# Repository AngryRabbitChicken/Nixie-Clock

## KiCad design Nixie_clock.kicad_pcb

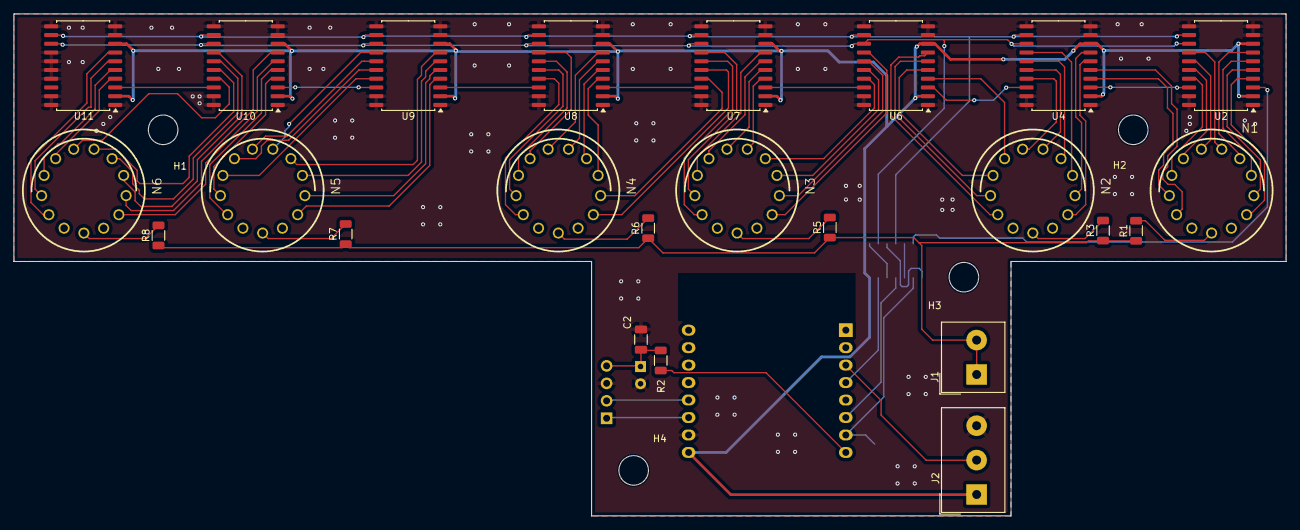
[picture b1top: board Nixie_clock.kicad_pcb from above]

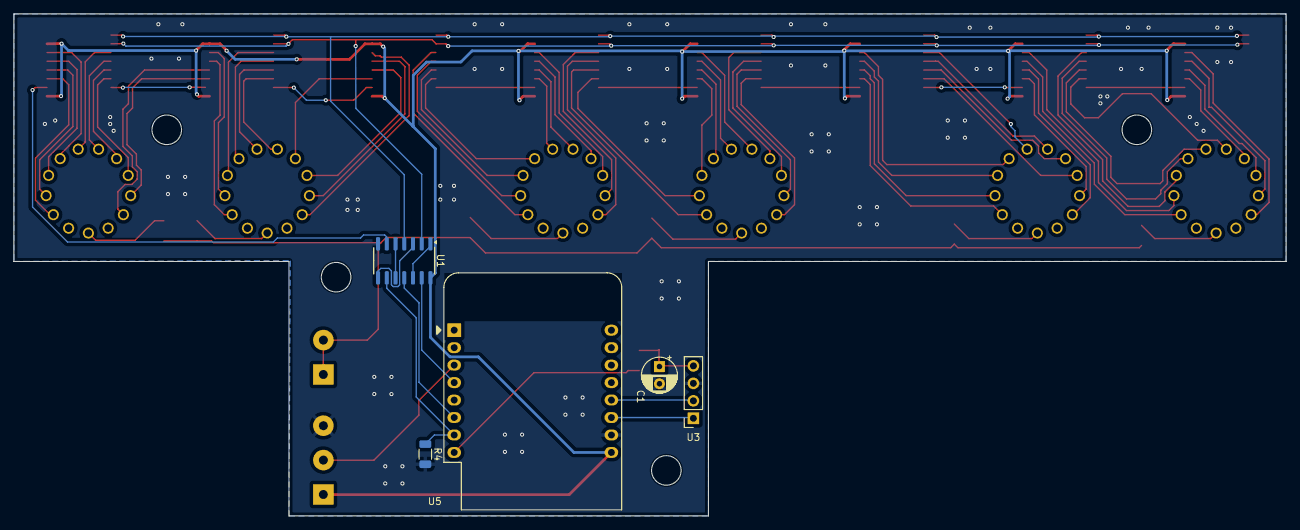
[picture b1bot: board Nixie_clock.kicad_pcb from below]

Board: 2 copper layers, 185.0 x 73.0 mm, 33 parts (5 on the bottom side), 90 nets.

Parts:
C1: 10µ; CP_Radial_D5.0mm_P2.50mm
C2: 1µ; C_1206_3216Metric
H1, H2, H3, H4: MountingHole; MountingHole_4.3mm_M4
J1: Screw_Terminal_01x02; Altech_AK100_1x02_P5.00mm
J2: Screw_Terminal_01x03; Altech_AK100_1x03_P5.00mm
N1, N2, N3, N4, N5, N6: IN-14; nixies-us-IN-14_1.1mm_holes
R1, R3, R5, R6, R7, R8: 21.5k; R_1206_3216Metric
R2: 100; R_1206_3216Metric
R4: 10k; R_1206_3216Metric
U1: 74HCT04; SO-14_3.9x8.65mm_P1.27mm
U2, U4, U6, U7, U8, U9, U10, U11: TPIC6B595; SOIC-20W_7.5x12.8mm_P1.27mm
U3: Pollin_DCF1; PinSocket_1x04_P2.54mm_Vertical
U5: WeMos_D1_mini; WEMOS_D1_mini_light

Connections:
167V: J1.1, J1.2, R1.1, R3.1, R5.1, R6.1, R7.1, R8.1
+3.3V: R2.1, U5.8 (3V3)
+5V: J2.1, U1.14 (VCC), U2.2 (VCC), U2.8 (~SRCLR), U4.2 (VCC), U4.8 (~SRCLR), U5.9 (5V), U6.2 (VCC), U6.8 (~SRCLR), U7.2 (VCC), U7.8 (~SRCLR), U8.2 (VCC), U8.8 (~SRCLR), U9.2 (VCC), U9.8 (~SRCLR), U10.2 (VCC), U10.8 (~SRCLR), U11.2 (VCC), U11.8 (~SRCLR)
/N1-A: N1.A, R1.2
/N2-A: N2.A, R3.2
/N3-A: N3.A, R5.2
/N4-A: N4.A, R6.2
/N5-A: N5.A, R7.2
/N6-A: N6.A, R8.2
/U2-D0: N1.1, U2.4 (DRAIN0)
/U2-D1: N1.2, U2.5 (DRAIN1)
/U2-D2: N1.3, U2.6 (DRAIN2)
/U2-D3: N1.4, U2.7 (DRAIN3)
/U2-D4: N1.5, U2.14 (DRAIN4)
/U2-D5: N1.6, U2.15 (DRAIN5)
/U2-D6: N1.7, U2.16 (DRAIN6)
/U2-D7: N1.8, U2.17 (DRAIN7)
/U4-D0: N1.9, U4.4 (DRAIN0)
/U4-D1: N1.0, U4.5 (DRAIN1)
/U4-D2: N2.1, U4.6 (DRAIN2)
/U4-D3: N2.2, U4.7 (DRAIN3)
/U4-D4: N2.3, U4.14 (DRAIN4)
/U4-D5: N2.4, U4.15 (DRAIN5)
/U4-D6: N2.5, U4.16 (DRAIN6)
/U4-D7: N2.6, U4.17 (DRAIN7)
/U6-D0: N2.7, U6.4 (DRAIN0)
/U6-D1: N2.8, U6.5 (DRAIN1)
/U6-D2: N2.9, U6.6 (DRAIN2)
/U6-D3: N2.0, U6.7 (DRAIN3)
/U6-D4: N3.1, U6.14 (DRAIN4)
/U6-D5: N3.2, U6.15 (DRAIN5)
/U6-D6: N3.3, U6.16 (DRAIN6)
/U6-D7: N3.4, U6.17 (DRAIN7)
/U7-D0: N3.5, U7.4 (DRAIN0)
/U7-D1: N3.6, U7.5 (DRAIN1)
/U7-D2: N3.7, U7.6 (DRAIN2)
/U7-D3: N3.8, U7.7 (DRAIN3)
/U7-D4: N3.9, U7.14 (DRAIN4)
/U7-D5: N3.0, U7.15 (DRAIN5)
/U7-D6: N4.1, U7.16 (DRAIN6)
/U7-D7: N4.2, U7.17 (DRAIN7)
/U8-D0: N4.3, U8.4 (DRAIN0)
/U8-D1: N4.4, U8.5 (DRAIN1)
/U8-D2: N4.5, U8.6 (DRAIN2)
/U8-D3: N4.6, U8.7 (DRAIN3)
/U8-D4: N4.7, U8.14 (DRAIN4)
/U8-D5: N4.8, U8.15 (DRAIN5)
/U8-D6: N4.9, U8.16 (DRAIN6)
/U8-D7: N4.0, U8.17 (DRAIN7)
/U9-D0: N5.1, U9.4 (DRAIN0)
/U9-D1: N5.2, U9.5 (DRAIN1)
/U9-D2: N5.3, U9.6 (DRAIN2)
/U9-D3: N5.4, U9.7 (DRAIN3)
/U9-D4: N5.5, U9.14 (DRAIN4)
/U9-D5: N5.6, U9.15 (DRAIN5)
/U9-D6: N5.7, U9.16 (DRAIN6)
/U9-D7: N5.8, U9.17 (DRAIN7)
/U10-D0: N5.9, U10.4 (DRAIN0)
/U10-D1: N5.0, U10.5 (DRAIN1)
/U10-D2: N6.1, U10.6 (DRAIN2)
/U10-D3: N6.2, U10.7 (DRAIN3)
/U10-D4: N6.3, U10.14 (DRAIN4)
/U10-D5: N6.4, U10.15 (DRAIN5)
/U10-D6: N6.5, U10.16 (DRAIN6)
/U10-D7: N6.6, U10.17 (DRAIN7)
/U11-D0: N6.7, U11.4 (DRAIN0)
/U11-D1: N6.8, U11.5 (DRAIN1)
/U11-D2: N6.9, U11.6 (DRAIN2)
/U11-D3: N6.0, U11.7 (DRAIN3)
GND: C1.2, C2.2, J2.3, R4.2, U1.7 (GND), U2.1 (PGND), U2.9 (~G), U2.10 (PGND), U2.11 (PGND), U2.19 (LGND), U2.20 (PGND), U3.3 (GND), U4.1 (PGND), U4.9 (~G), U4.10 (PGND), U4.11 (PGND), U4.19 (LGND), U4.20 (PGND), U5.10 (GND), U6.1 (PGND), U6.9 (~G), U6.10 (PGND), U6.11 (PGND), U6.19 (LGND), U6.20 (PGND), U7.1 (PGND), U7.9 (~G), U7.10 (PGND), U7.11 (PGND), U7.19 (LGND), U7.20 (PGND), U8.1 (PGND), U8.9 (~G), U8.10 (PGND), U8.11 (PGND), U8.19 (LGND), U8.20 (PGND), U9.1 (PGND), U9.9 (~G), U9.10 (PGND), U9.11 (PGND), U9.19 (LGND), U9.20 (PGND), U10.1 (PGND), U10.9 (~G), U10.10 (PGND), U10.11 (PGND), U10.19 (LGND), U10.20 (PGND), U11.1 (PGND), U11.9 (~G), U11.10 (PGND), U11.11 (PGND), U11.14 (DRAIN4), U11.15 (DRAIN5), U11.16 (DRAIN6), U11.17 (DRAIN7), U11.19 (LGND), U11.20 (PGND)
HV_ENABLE: J2.2, U5.3 (D0)
unnamed: U1.1, U1.12
unnamed: U1.3, U1.8
unnamed: U1.5, U1.10
unnamed: U1.6, U2.3 (SER_IN)
unnamed: U2.18 (SER_OUT), U4.3 (SER_IN)
unnamed: U3.1 (PON), U5.11 (D4)
unnamed: U3.2 (TCO), U5.12 (D3)
unnamed: C1.1, C2.1, R2.2, U3.4 (VCC)
unnamed: U4.18 (SER_OUT), U6.3 (SER_IN)
unnamed: R4.1, U1.9, U5.7 (CS/D8)
unnamed: U1.11, U5.6 (MOSI/D7)
unnamed: U1.13, U5.4 (SCK/D5)
unnamed: U6.18 (SER_OUT), U7.3 (SER_IN)
unnamed: U7.18 (SER_OUT), U8.3 (SER_IN)
unnamed: U8.18 (SER_OUT), U9.3 (SER_IN)
unnamed: U1.4, U2.12 (RCLK), U4.12 (RCLK), U6.12 (RCLK), U7.12 (RCLK), U8.12 (RCLK), U9.12 (RCLK), U10.12 (RCLK), U11.12 (RCLK)
unnamed: U9.18 (SER_OUT), U10.3 (SER_IN)
unnamed: U10.18 (SER_OUT), U11.3 (SER_IN)
unnamed: U1.2, U2.13 (SRCK), U4.13 (SRCK), U6.13 (SRCK), U7.13 (SRCK), U8.13 (SRCK), U9.13 (SRCK), U10.13 (SRCK), U11.13 (SRCK)

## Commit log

2024-08-20 Initial Nixie-Clock Design, Circuit diagram finished, wiring needs to be done.
2024-08-28 First version of complete board
2024-08-28 Added the ignore file for the logs
2024-08-28 The Nixie PSU now fits seemlessly into the bottom right corner of the PCB
